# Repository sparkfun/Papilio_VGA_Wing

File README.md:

Papilio VGA Wing
================

[  
*Papilio VGA Wing (WIG-11569)*](https://www.sparkfun.com/products/11569)

This board allows you to quickly add VGA output to your Papilio FPGA board. 

Repository Contents
-------------------
* **/Hardware** - All Eagle design files (.brd, .sch)
* **/Production** - Test bed files and production panel files

License Information
-------------------
The hardware is released under [Creative Commons Share-alike 3.0](http://creativecommons.org/licenses/by-sa/3.0/).

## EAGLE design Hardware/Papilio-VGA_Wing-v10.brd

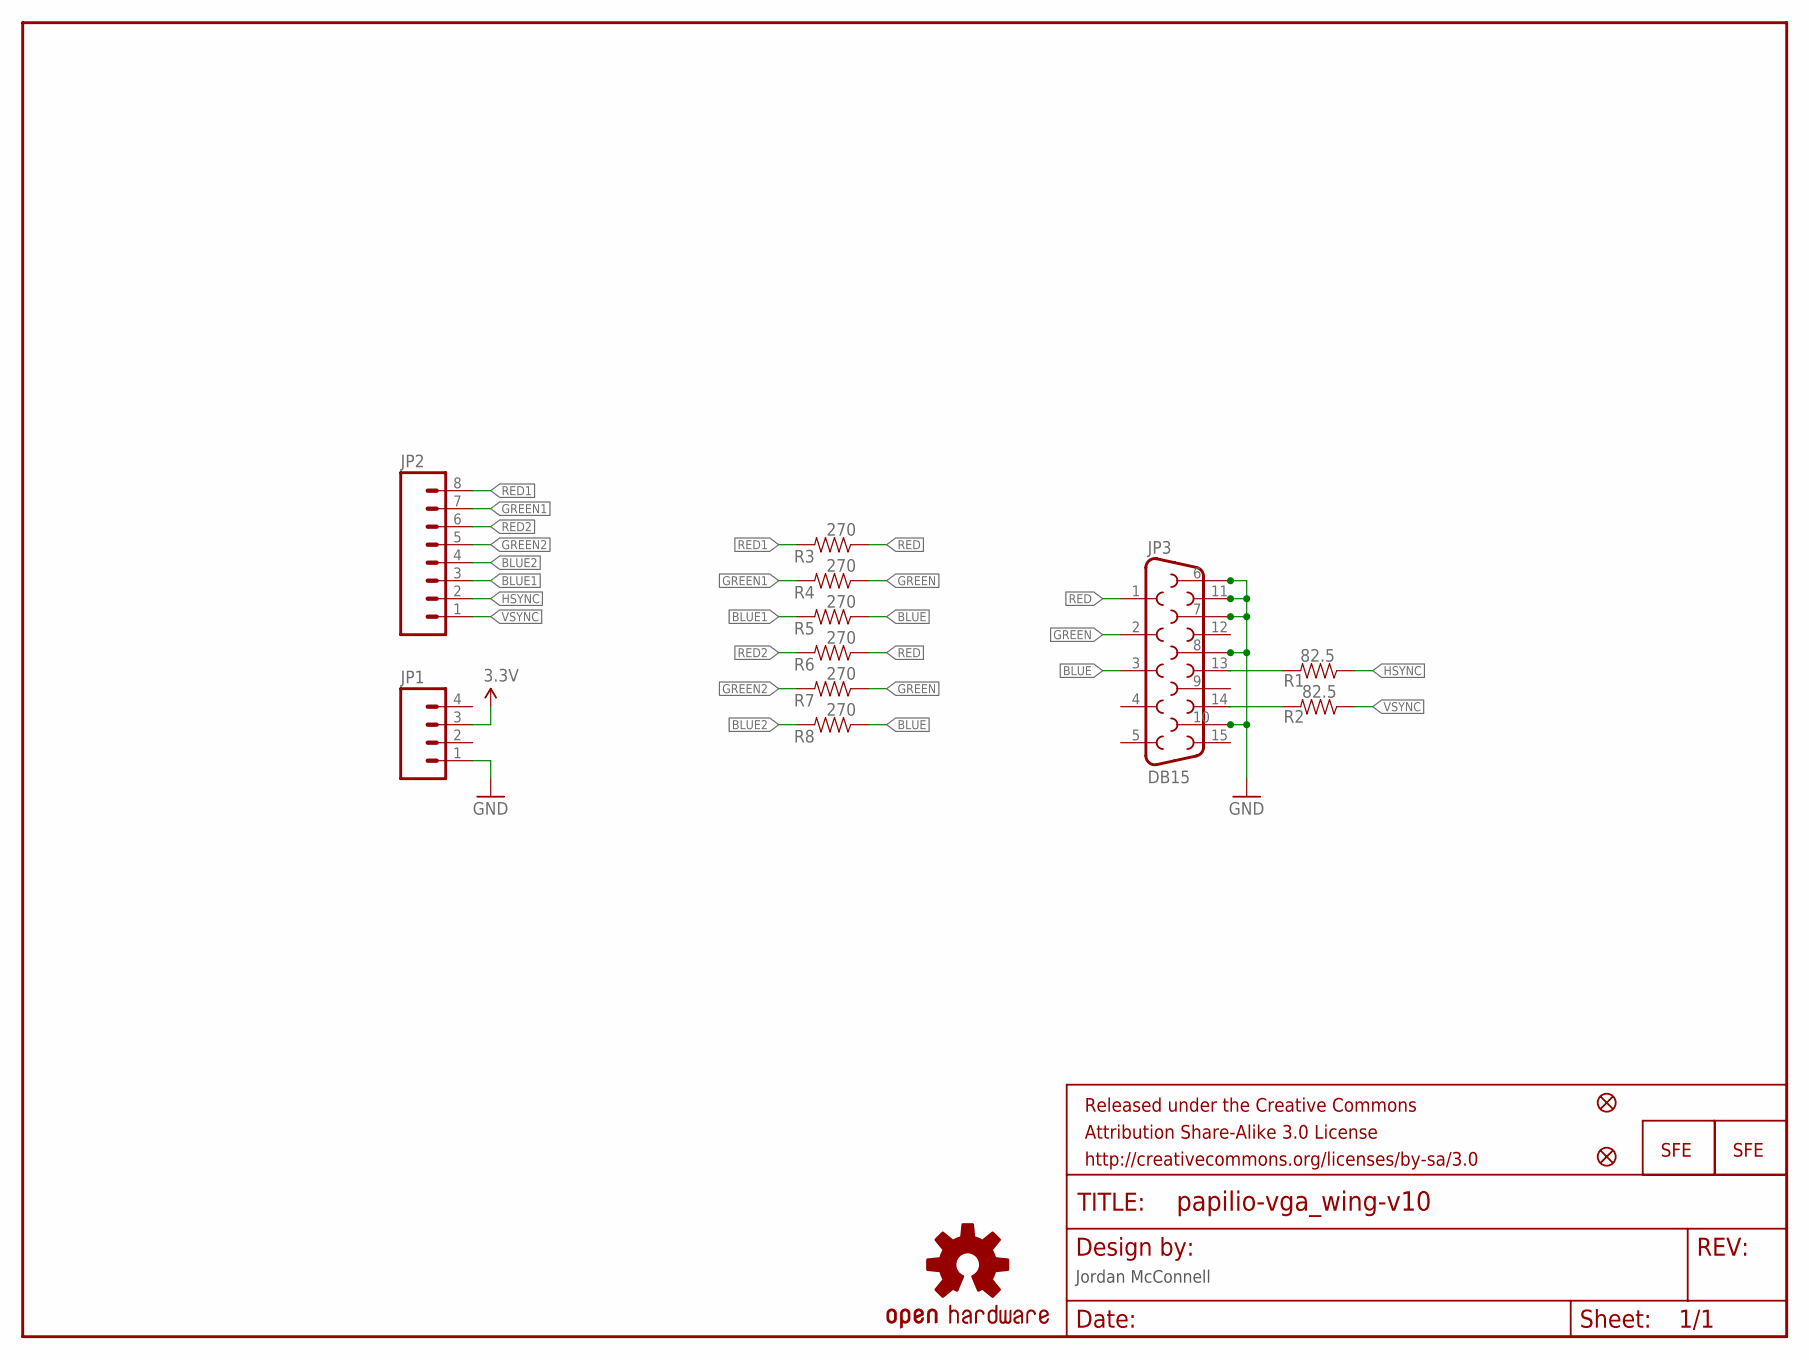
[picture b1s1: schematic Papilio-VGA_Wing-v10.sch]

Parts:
FRAME1: FRAME-LETTER; CREATIVE_COMMONS
JP1: M04PTH; 1X04
JP2: M081X08; 1X08
JP3: DB15
JP4, JP5: FIDUCIALUFIDUCIAL; MICRO-FIDUCIAL
JP6: LOGO-SFENEW; SFE-NEW-WEBLOGO
JP7: LOGO-SFESK; SFE-LOGO-FLAME
R1, R2: 82.5; 0402-RES
R3, R4, R5, R6, R7, R8: 270; 0402-RES
U$1: OSHW-LOGOS; OSHW-LOGO-S

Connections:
3.3V: JP1.3
BLUE: JP3.3, R5.1, R8.1
BLUE1: JP2.3, R5.2
BLUE2: JP2.4, R8.2
GND: JP1.1, JP3.6, JP3.7, JP3.8, JP3.10, JP3.11
GREEN: JP3.2, R4.1, R7.1
GREEN1: JP2.7, R4.2
GREEN2: JP2.5, R7.2
HSYNC: JP2.2, R1.1
unnamed: JP3.13, R1.2
unnamed: JP3.14, R2.2
RED: JP3.1, R3.1, R6.1
RED1: JP2.8, R3.2
RED2: JP2.6, R6.2
VSYNC: JP2.1, R2.1

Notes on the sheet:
Jordan McConnell

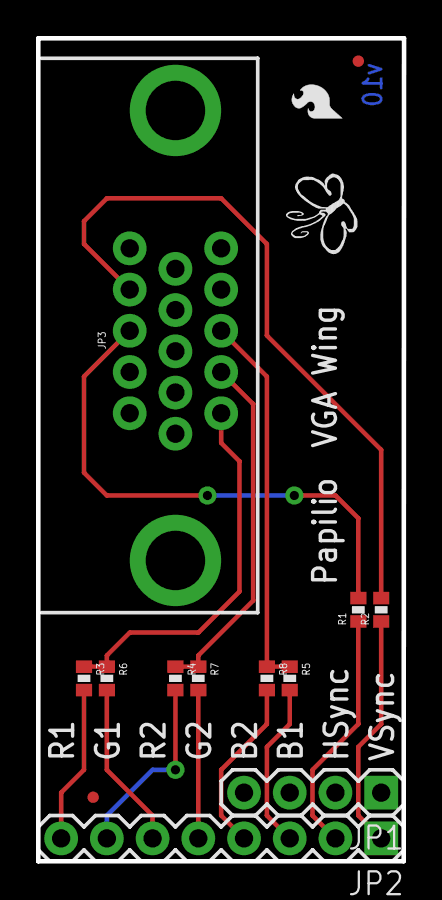
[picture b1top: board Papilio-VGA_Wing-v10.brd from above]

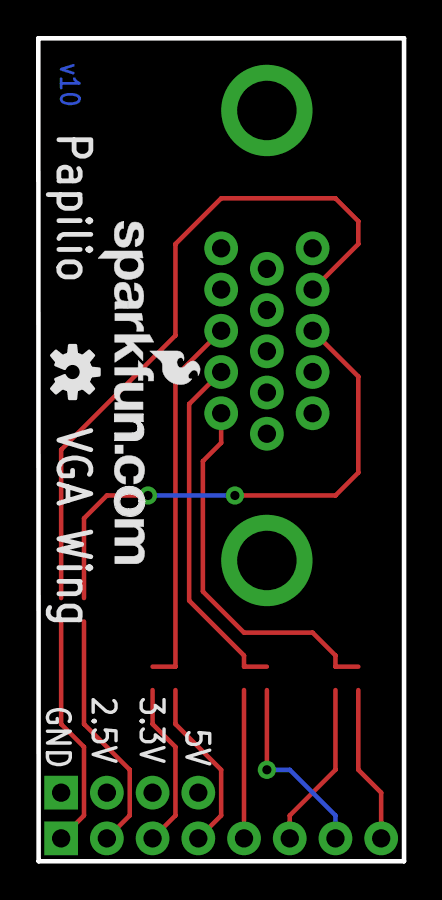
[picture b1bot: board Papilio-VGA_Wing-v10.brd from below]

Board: 2 copper layers, 20.3 x 45.7 mm, 17 parts (2 on the bottom side), 14 nets.

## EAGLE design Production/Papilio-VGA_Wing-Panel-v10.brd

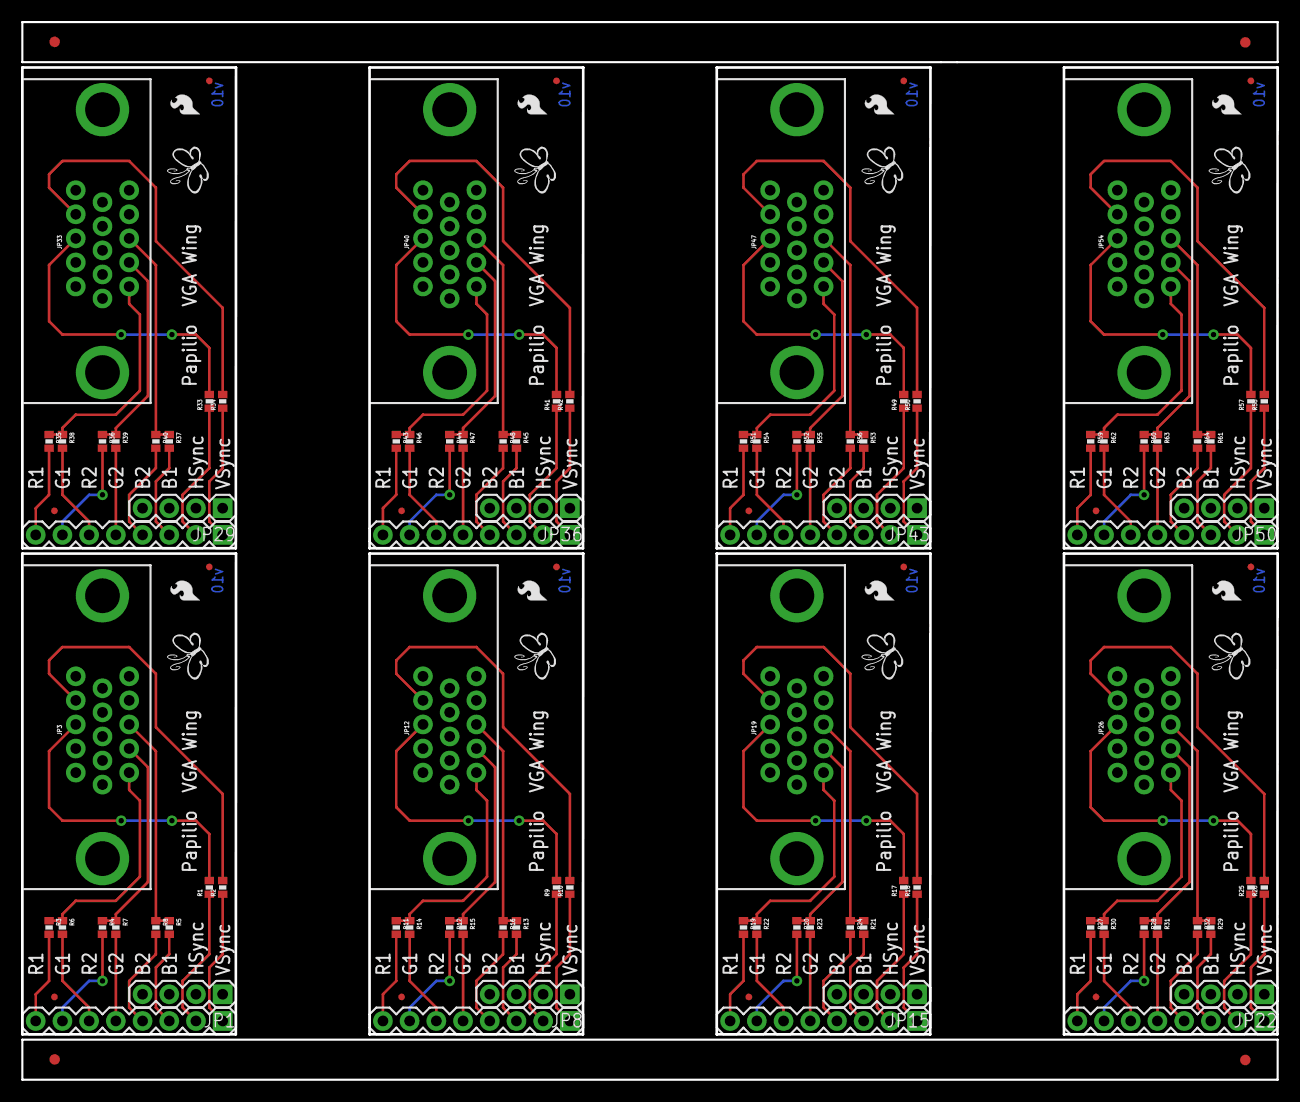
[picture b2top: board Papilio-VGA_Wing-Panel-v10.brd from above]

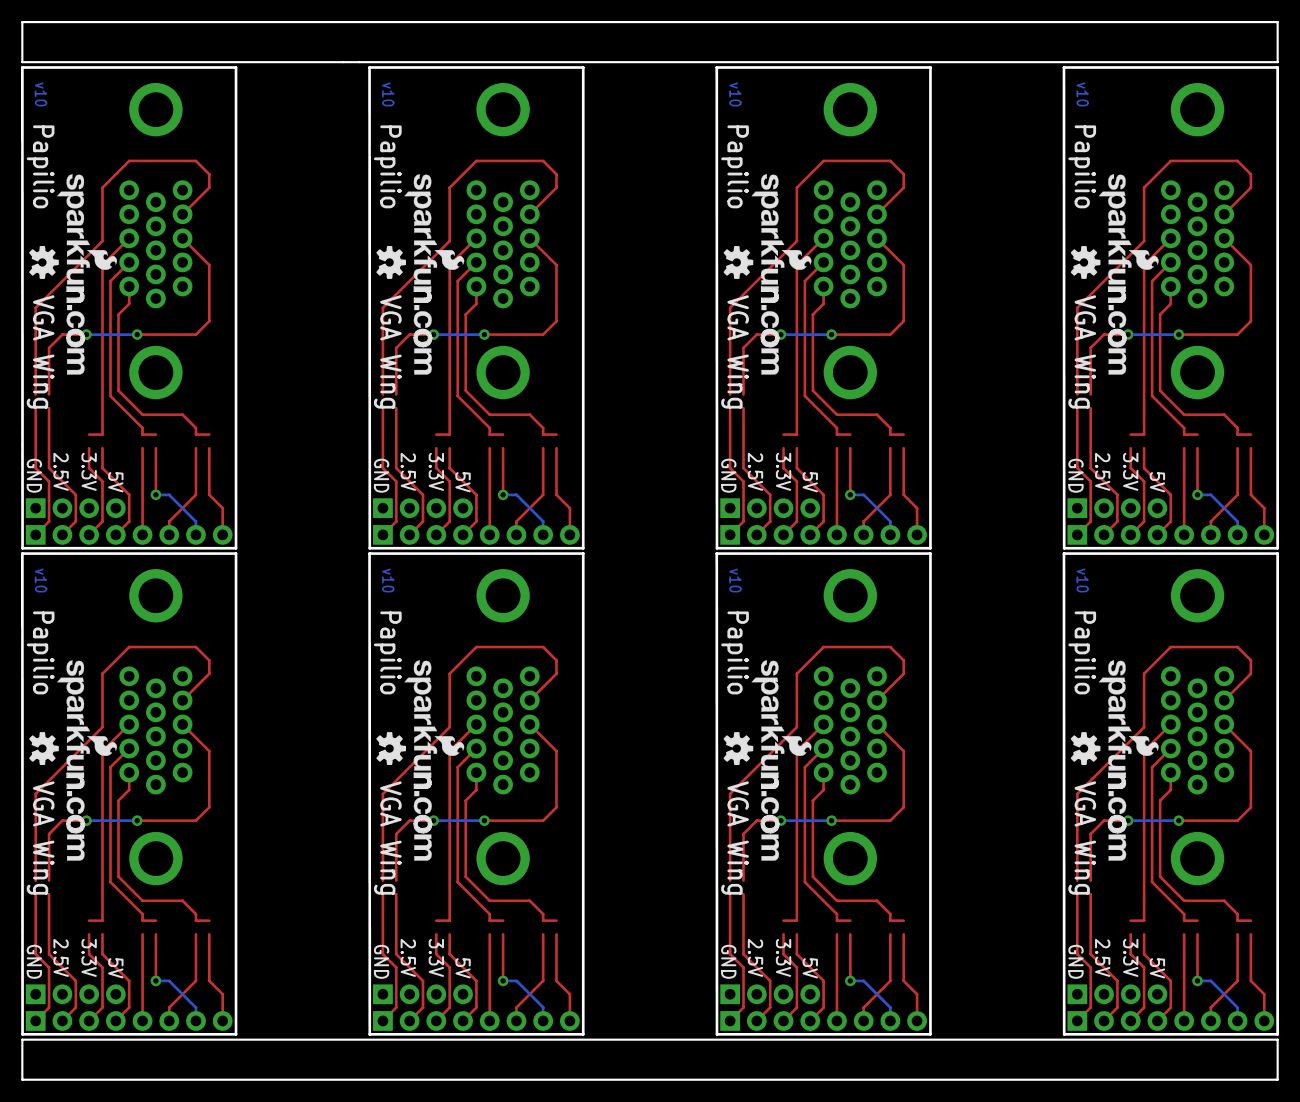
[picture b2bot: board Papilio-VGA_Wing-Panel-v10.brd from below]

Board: 2 copper layers, 119.4 x 100.5 mm, 132 parts (16 on the bottom side), 112 nets.

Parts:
E$1, E$2, E$3, E$4: FIDUCIAL-1X2
JP1, JP8, JP15, JP22, JP29, JP36, JP43, JP50: 1X04
JP2, JP9, JP16, JP23, JP30, JP37, JP44, JP51: 1X08
JP3, JP12, JP19, JP26, JP33, JP40, JP47, JP54: DB15
JP4, JP5, JP13, JP14, JP20, JP21, JP27, JP28, JP34, JP35, JP41, JP42, JP48, JP49, JP55, JP56: FIDUCIALUFIDUCIAL; MICRO-FIDUCIAL
JP6, JP11, JP18, JP25, JP32, JP39, JP46, JP53: LOGO-SFENEW; SFE-NEW-WEBLOGO
JP7, JP10, JP17, JP24, JP31, JP38, JP45, JP52: LOGO-SFESK; SFE-LOGO-FLAME
R1, R2, R9, R10, R17, R18, R25, R26, R33, R34, R41, R42, R49, R50, R57, R58: 82.5; 0402-RES
R3, R4, R5, R6, R7, R8, R11, R12, R13, R14, R15, R16, R19, R20, R21, R22, R23, R24, R27, R28, R29, R30, R31, R32, R35, R36, R37, R38, R39, R40, R43, R44, R45, R46, R47, R48, R51, R52, R53, R54, R55, R56, R59, R60, R61, R62, R63, R64: 270; 0402-RES
U$1, U$2, U$3, U$4, U$5, U$6, U$7, U$8: OSHW-LOGOS; OSHW-LOGO-S

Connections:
BLUE: JP3.3, R5.1, R8.1
BLUE1: JP2.3, R5.2
BLUE2: JP2.4, R8.2
BLUE3: JP9.3, R13.2
BLUE4: JP9.4, R16.2
BLUE5: JP12.3, R13.1, R16.1
BLUE6: JP16.3, R21.2
BLUE7: JP16.4, R24.2
BLUE8: JP19.3, R21.1, R24.1
BLUE9: JP23.3, R29.2
BLUE10: JP23.4, R32.2
BLUE11: JP26.3, R29.1, R32.1
BLUE12: JP30.3, R37.2
BLUE13: JP30.4, R40.2
BLUE14: JP33.3, R37.1, R40.1
BLUE15: JP37.3, R45.2
BLUE16: JP37.4, R48.2
BLUE17: JP40.3, R45.1, R48.1
BLUE18: JP44.3, R53.2
BLUE19: JP44.4, R56.2
BLUE20: JP47.3, R53.1, R56.1
BLUE21: JP51.3, R61.2
BLUE22: JP51.4, R64.2
BLUE23: JP54.3, R61.1, R64.1
GND: JP1.1, JP3.6, JP3.7, JP3.8, JP3.10, JP3.11
GND1: JP8.1, JP12.6, JP12.7, JP12.8, JP12.10, JP12.11
GND2: JP15.1, JP19.6, JP19.7, JP19.8, JP19.10, JP19.11
GND3: JP22.1, JP26.6, JP26.7, JP26.8, JP26.10, JP26.11
GND4: JP29.1, JP33.6, JP33.7, JP33.8, JP33.10, JP33.11
GND5: JP36.1, JP40.6, JP40.7, JP40.8, JP40.10, JP40.11
GND6: JP43.1, JP47.6, JP47.7, JP47.8, JP47.10, JP47.11
GND7: JP50.1, JP54.6, JP54.7, JP54.8, JP54.10, JP54.11
GREEN: JP3.2, R4.1, R7.1
GREEN1: JP2.7, R4.2
GREEN2: JP2.5, R7.2
GREEN3: JP9.7, R12.2
GREEN4: JP9.5, R15.2
GREEN5: JP12.2, R12.1, R15.1
GREEN6: JP16.7, R20.2
GREEN7: JP16.5, R23.2
GREEN8: JP19.2, R20.1, R23.1
GREEN9: JP23.7, R28.2
GREEN10: JP23.5, R31.2
GREEN11: JP26.2, R28.1, R31.1
GREEN12: JP30.7, R36.2
GREEN13: JP30.5, R39.2
GREEN14: JP33.2, R36.1, R39.1
GREEN15: JP37.7, R44.2
GREEN16: JP37.5, R47.2
GREEN17: JP40.2, R44.1, R47.1
GREEN18: JP44.7, R52.2
GREEN19: JP44.5, R55.2
GREEN20: JP47.2, R52.1, R55.1
GREEN21: JP51.7, R60.2
GREEN22: JP51.5, R63.2
GREEN23: JP54.2, R60.1, R63.1
HSYNC: JP2.2, R1.1
HSYNC1: JP9.2, R9.1
HSYNC2: JP16.2, R17.1
HSYNC3: JP23.2, R25.1
HSYNC4: JP30.2, R33.1
HSYNC5: JP37.2, R41.1
HSYNC6: JP44.2, R49.1
HSYNC7: JP51.2, R57.1
unnamed: JP12.13, R9.2
unnamed: JP3.13, R1.2
unnamed: JP3.14, R2.2
unnamed: JP12.14, R10.2
unnamed: JP19.13, R17.2
unnamed: JP19.14, R18.2
unnamed: JP26.13, R25.2
unnamed: JP26.14, R26.2
unnamed: JP33.13, R33.2
unnamed: JP33.14, R34.2
unnamed: JP40.13, R41.2
unnamed: JP40.14, R42.2
unnamed: JP47.13, R49.2
unnamed: JP47.14, R50.2
unnamed: JP54.13, R57.2
unnamed: JP54.14, R58.2
RED: JP3.1, R3.1, R6.1
RED1: JP2.8, R3.2
RED2: JP2.6, R6.2
RED3: JP9.8, R11.2
RED4: JP9.6, R14.2
RED5: JP12.1, R11.1, R14.1
RED6: JP16.8, R19.2
RED7: JP16.6, R22.2
RED8: JP19.1, R19.1, R22.1
RED9: JP23.8, R27.2
RED10: JP23.6, R30.2
RED11: JP26.1, R27.1, R30.1
RED12: JP30.8, R35.2
RED13: JP30.6, R38.2
RED14: JP33.1, R35.1, R38.1
RED15: JP37.8, R43.2
RED16: JP37.6, R46.2
RED17: JP40.1, R43.1, R46.1
RED18: JP44.8, R51.2
RED19: JP44.6, R54.2
RED20: JP47.1, R51.1, R54.1
RED21: JP51.8, R59.2
RED22: JP51.6, R62.2
RED23: JP54.1, R59.1, R62.1
VSYNC: JP2.1, R2.1
VSYNC1: JP9.1, R10.1
VSYNC2: JP16.1, R18.1
VSYNC3: JP23.1, R26.1
VSYNC4: JP30.1, R34.1
VSYNC5: JP37.1, R42.1
VSYNC6: JP44.1, R50.1
VSYNC7: JP51.1, R58.1

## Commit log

2013-08-19 Initial file commit
2013-08-19 Removing duplicate files

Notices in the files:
parts and their libraries:
SparkFun-Aesthetics: Licensing: CC v3.0 Share-Alike You are welcome to use this library for commercial purposes.
SparkFun-Aesthetics: Released under the Creative Commons Attribution Share-Alike 3.0 License
SparkFun-Aesthetics: Released under the Creative Commons
